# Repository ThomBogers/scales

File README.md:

WIP

WIFI Connected scales

The board should be able to weigh me and send the data to a server

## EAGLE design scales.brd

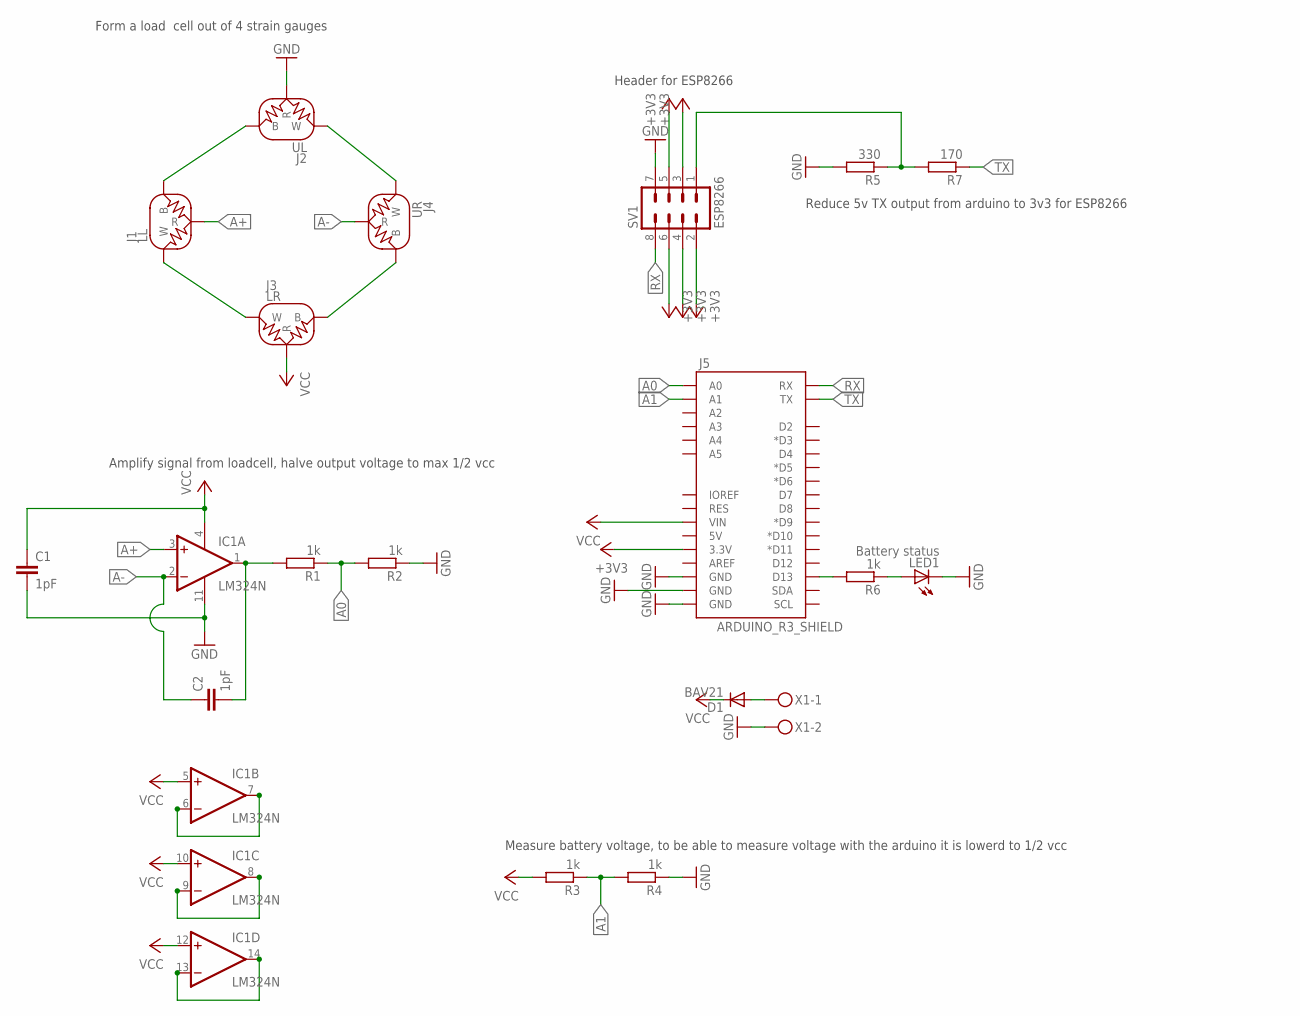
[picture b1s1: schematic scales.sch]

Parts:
C1, C2: 1pF; C025-024X044
D1: BAV21; DO35-10
IC1: LM324N; DIL14; MPN LM324AN
J1: LL; 1X03
J2: UL; 1X03
J3: LR; 1X03
J4: UR; 1X03
J5: ARDUINO_R3_SHIELD; UNO_R3_SHIELD
LED1: Battery status; LED5MM
R1, R2, R3, R4, R6: 1k; 0204/5; MPN ERG1SJ102
R5: 330; 0204/5; MPN ERG1SJ102
R7: 170; 0204/5; MPN ERG1SJ102
SV1: ESP8266; MA04-2; MPN BD060-08-A-N-0230-L-G
X1: MKDSN1,5/2-5,08

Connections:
+3V3: J5.3.3V, SV1.2, SV1.3, SV1.4, SV1.5, SV1.6
A0: J5.A0, R1.1, R2.2
A1: J5.A1, R3.1, R4.2
A+: IC1.3 (+IN), J1.3 (R)
A-: C2.1, IC1.2 (-IN), J4.3 (R)
GND: C1.2, IC1.11 (V-), J2.3 (R), J5.GND@0 (GND), J5.GND@1 (GND), J5.GND@2 (GND), LED1.K (C), R2.1, R4.1, R5.2, SV1.7, X1.2
unnamed: IC1.6 (-IN), IC1.7 (OUT)
unnamed: IC1.8 (OUT), IC1.9 (-IN)
unnamed: IC1.13 (-IN), IC1.14 (OUT)
unnamed: D1.A, X1.1
unnamed: J5.D13, R6.2
unnamed: C2.2, IC1.1 (OUT), R1.2
unnamed: LED1.A, R6.1
unnamed: R5.1, R7.2, SV1.1
unnamed: J1.1 (B), J2.1 (B)
unnamed: J3.1 (B), J4.1 (B)
unnamed: J2.2 (W), J4.2 (W)
unnamed: J1.2 (W), J3.2 (W)
RX: J5.RX, SV1.8
TX: J5.TX, R7.1
VCC: C1.1, D1.C, IC1.4 (V+), IC1.5 (+IN), IC1.10 (+IN), IC1.12 (+IN), J3.3 (R), J5.VIN, R3.2

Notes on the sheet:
Form a load cell out of 4 strain gauges
Amplify signal from loadcell, halve output voltage to max 1/2 vcc
Measure battery voltage, to be able to measure voltage with the arduino it is lowerd to 1/2 vcc
Header for ESP8266
Reduce 5v TX output from arduino to 3v3 for ESP8266

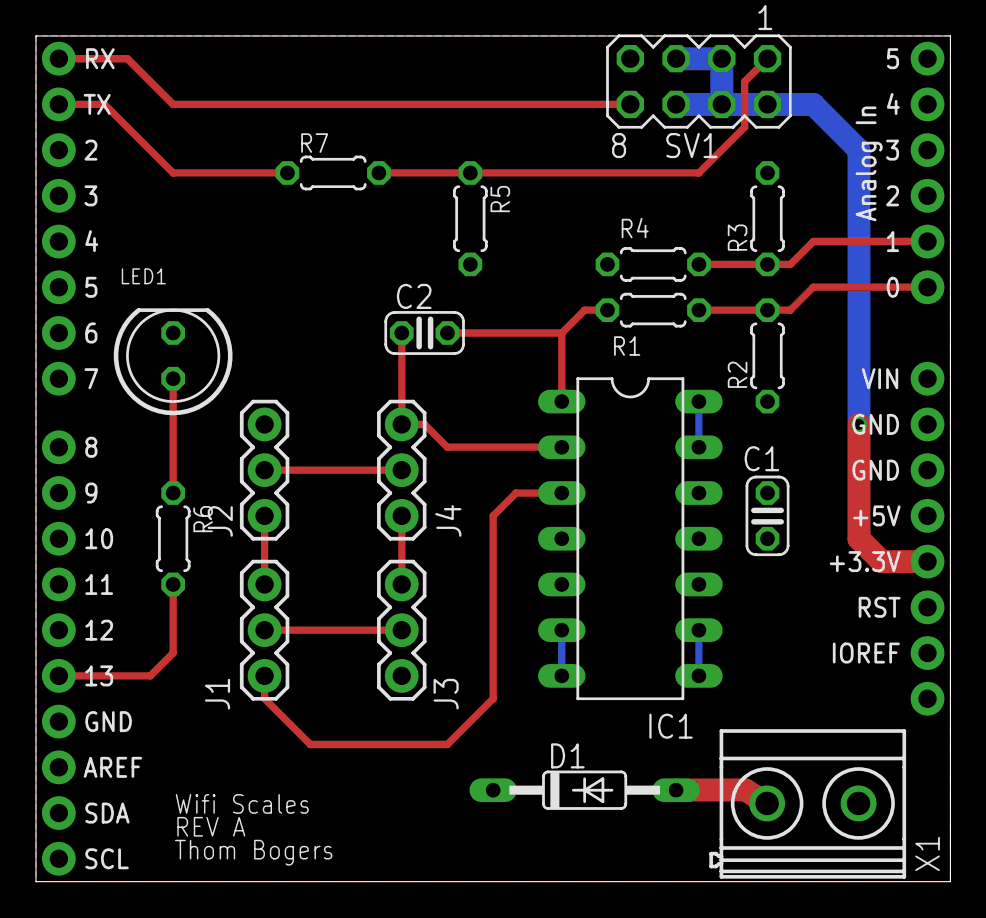
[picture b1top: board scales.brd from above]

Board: 2 copper layers, 50.8 x 47.0 mm, 19 parts (0 on the bottom side), 21 nets.

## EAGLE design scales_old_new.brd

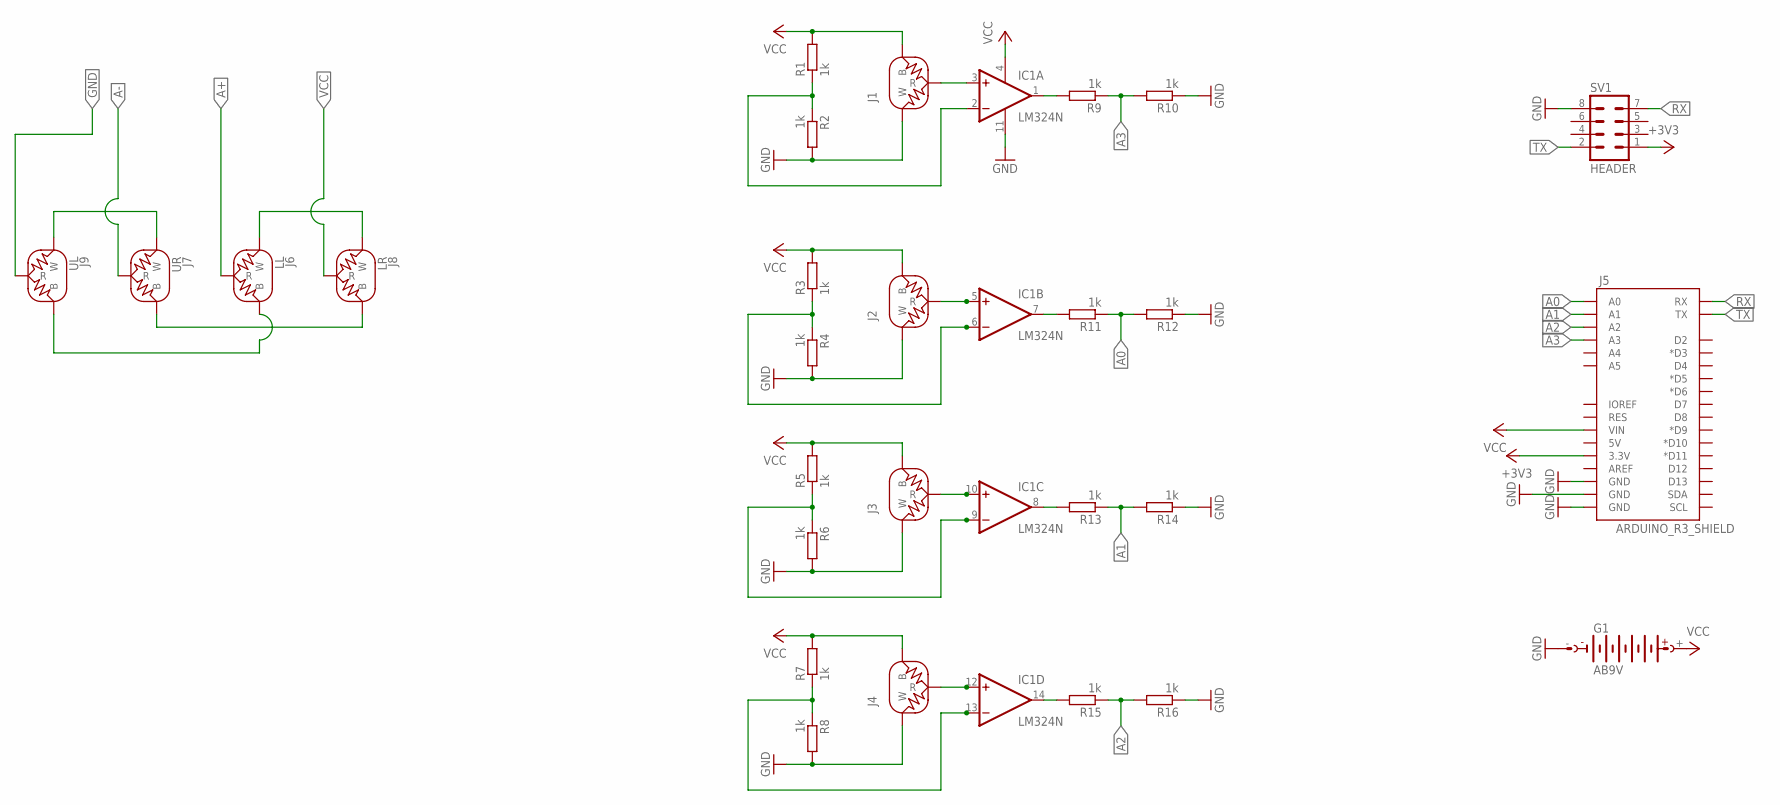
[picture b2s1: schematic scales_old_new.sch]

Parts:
G1: AB9V; MPN 440005P
IC1: LM324N; DIL14; MPN LM324AN
J1, J2, J3, J4: LOAD_CELL1X03-PTH; 1X03
J5: ARDUINO_R3_SHIELD; UNO_R3_SHIELD
J6: LL; 1X03
J7: UR; 1X03
J8: LR; 1X03
J9: UL; 1X03
R1, R2, R3, R4, R5, R6, R7, R8, R9, R10, R11, R12, R13, R14, R15, R16: 1k; 0204/5; MPN ERG1SJ102
SV1: HEADER; MA04-2; MPN BD060-08-A-N-0230-L-G

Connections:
+3V3: J5.3.3V, SV1.1
A0: J5.A0, R11.1, R12.2
A1: J5.A1, R13.1, R14.2
A2: J5.A2, R15.1, R16.2
A3: J5.A3, R9.1, R10.2
A+: J6.3 (R)
A-: J7.3 (R)
GND: G1.-, IC1.11 (V-), J1.2 (W), J2.2 (W), J3.2 (W), J4.2 (W), J5.GND@0 (GND), J5.GND@1 (GND), J5.GND@2 (GND), J9.3 (R), R2.2, R4.2, R6.2, R8.2, R10.1, R12.1, R14.1, R16.1, SV1.8
unnamed: IC1.5 (+IN), J2.3 (R)
unnamed: IC1.6 (-IN), R3.1, R4.1
unnamed: IC1.10 (+IN), J3.3 (R)
unnamed: IC1.9 (-IN), R5.1, R6.1
unnamed: IC1.2 (-IN), R1.1, R2.1
unnamed: IC1.1 (OUT), R9.2
unnamed: IC1.12 (+IN), J4.3 (R)
unnamed: IC1.13 (-IN), R7.1, R8.1
unnamed: IC1.7 (OUT), R11.2
unnamed: IC1.3 (+IN), J1.3 (R)
unnamed: IC1.8 (OUT), R13.2
unnamed: IC1.14 (OUT), R15.2
unnamed: J6.1 (B), J9.1 (B)
unnamed: J7.1 (B), J8.1 (B)
unnamed: J7.2 (W), J9.2 (W)
unnamed: J6.2 (W), J8.2 (W)
RX: J5.RX, SV1.7
TX: J5.TX, SV1.2
VCC: G1.+, IC1.4 (V+), J1.1 (B), J2.1 (B), J3.1 (B), J4.1 (B), J5.VIN, J8.3 (R), R1.2, R3.2, R5.2, R7.2

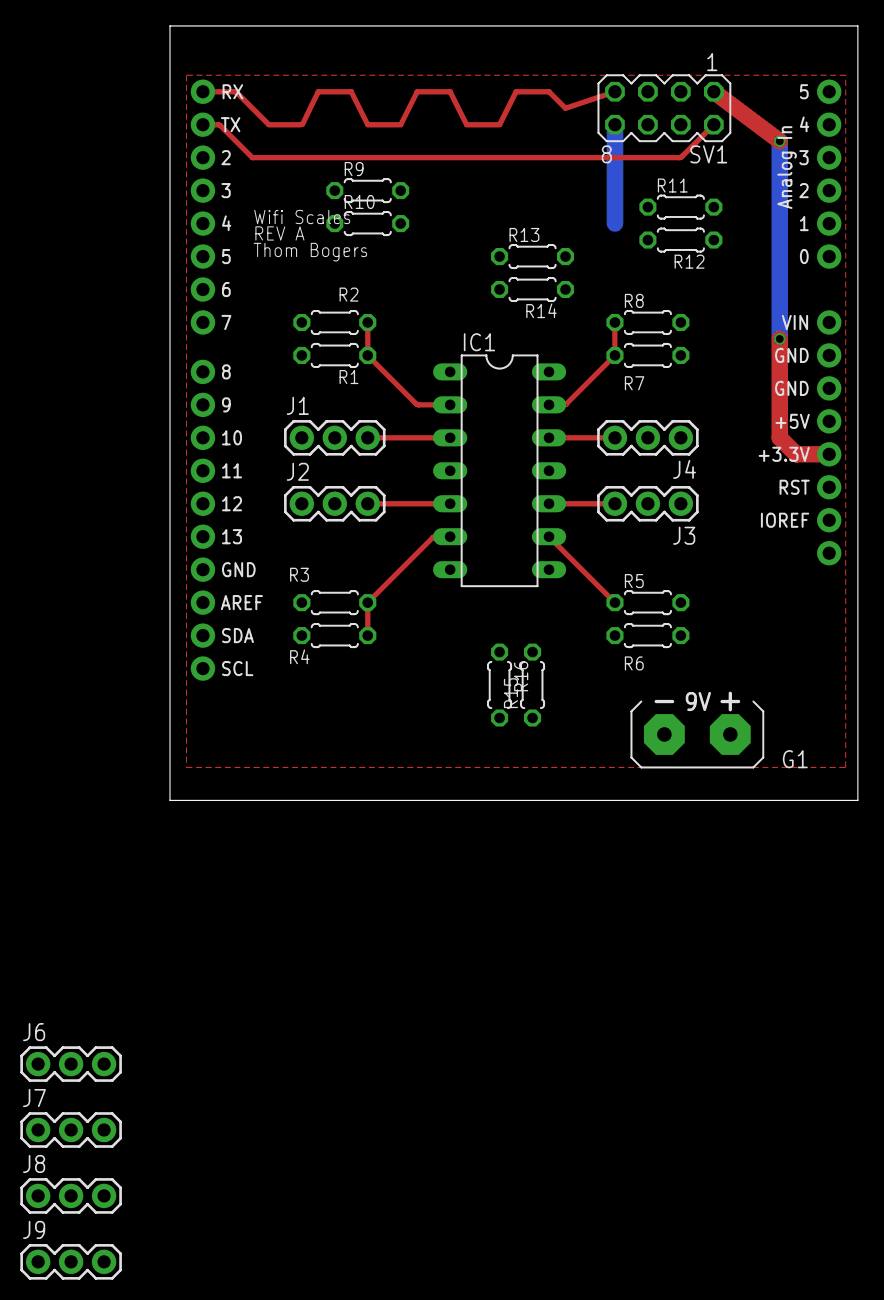
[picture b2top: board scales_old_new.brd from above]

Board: 2 copper layers, 53.0 x 59.7 mm, 28 parts (0 on the bottom side), 25 nets.

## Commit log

2018-02-01 Make into git repo
2018-02-01 Add the code to the eagle files

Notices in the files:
parts and their libraries:
SparkFun-Sensors: Licensing: Creative Commons ShareAlike 4.0 International - https://creativecommons.org/licenses/by-sa/4.0
